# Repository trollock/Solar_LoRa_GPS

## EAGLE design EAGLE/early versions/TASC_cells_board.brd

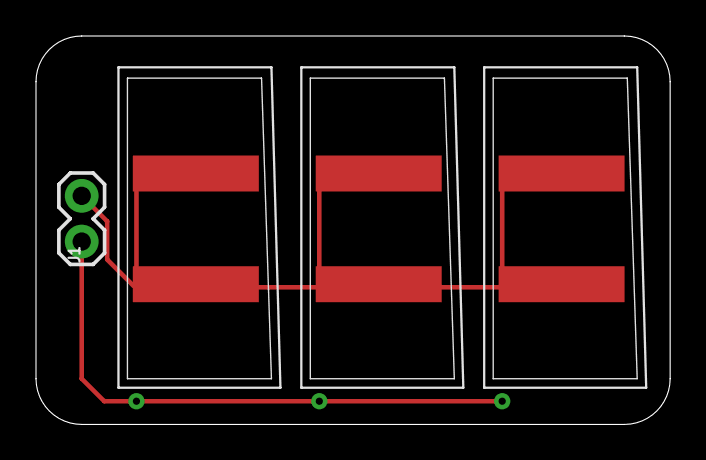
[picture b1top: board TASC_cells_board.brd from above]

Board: 2 copper layers, 35.2 x 21.6 mm, 4 parts (0 on the bottom side), 2 nets.

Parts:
J1: 1X02
U$1, U$2, U$3: TRISOLX_8X16

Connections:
NEG: J1.2, U$1.P$2, U$2.P$2, U$3.P$2
POS: J1.1, U$1.P$3, U$2.P$3, U$3.P$3

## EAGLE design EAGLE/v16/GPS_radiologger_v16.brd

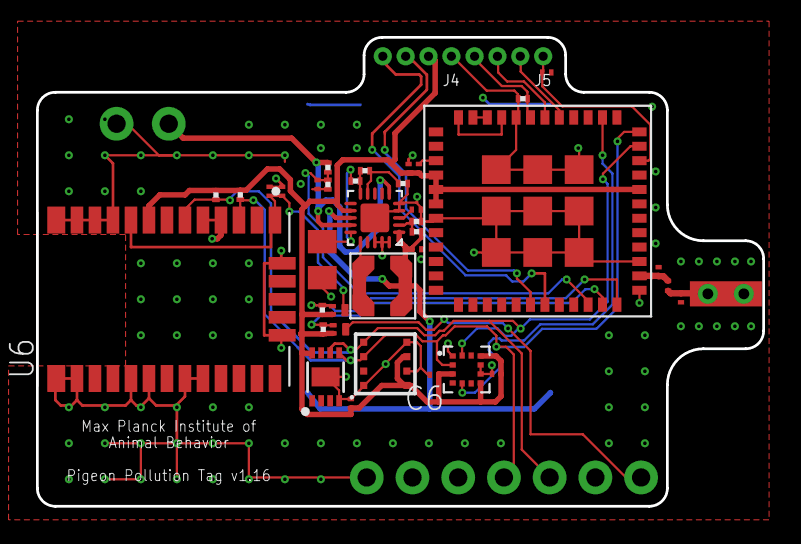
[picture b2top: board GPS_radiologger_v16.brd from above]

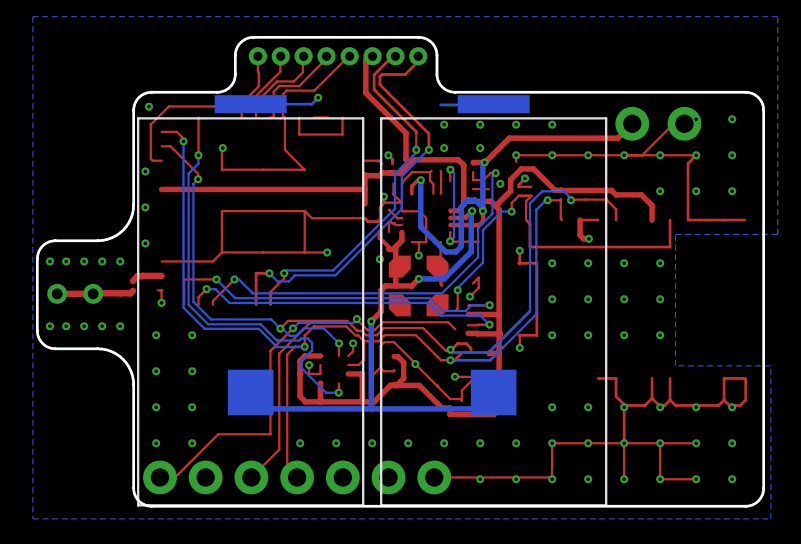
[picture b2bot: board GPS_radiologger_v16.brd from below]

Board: 2 copper layers, 40.4 x 26.1 mm, 44 parts (2 on the bottom side), 29 nets.

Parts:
C1, C3, C7, C10: 0.1 uF; C0201
C2: 47 uF; C0201
C4: 10nF; C0201
C5: 100 nF; C0201
C6, C8: C0201
C9: 1 uF; C0201
C11: 0.1uF; L0201
C13: 47 uF; C0805K
C14: 4.7 uF; C0201
IC4: CAT24M01HU5I-GT3; SON50P300X200X55-9N
J1, J3: 1X01_NO_SILK
J4, J5: 1X04_1.27MM_NO_SILK
J7: 1X07_NO_SILK
L3, L4: C0201
PDTA143TMB,1, PDTA143TMB,315: TINYPICO-PNPAMB; SOT883(B)
R1, R2: 4.7 k; R0201
R3: 10k; R0201
R4, R5: 100k; R0201
R6: 10 M; R0201
R7: 4.7 M; R0201
R8, R12: 3M; R0201
R9: 9.1M; R0201
R10: 6.2M; R0201
R11: 1M; R0201
U1: TYPEABZ
U2: BMA400; XDCR_BMA400
U4: SPV1050
U5: BME680BME680; LGA3.0X3.0
U6: CAM-M8Q-0; LCC100P960X1400X210-31N
U$1: LPS3015; LPS_3015
U$2: NITINOL_ANTENNA_SHORT; ICARUS_NITINOL_ANTENNA_SHORT
U$3, U$4: ICARUS_V4_RAW; ICARUS_FULL_TOP

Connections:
ACC_INT: U1.P$38, U2.5
BAT: J1.1, R7.2, U4.P$6, U4.P$14
BOOT: J5.4, R3.2, U1.P$43
GND: C1.2, C2.2, C3.2, C4.2, C5.2, C6.2, C7.2, C8.2, C9.1, C10.1, C13.2, C14.2, IC4.4, IC4.9, J3.1, J4.1, J7.1, J7.6, L3.2, L4.2, R3.1, R6.1, R9.1, R12.1, U1.P$3, U1.P$7, U1.P$25, U1.P$27, U1.P$44, U1.P$49, U1.P$50, U1.P$51, U1.P$52, U1.P$53, U1.P$54, U1.P$55, U1.P$56, U1.P$57, U2.1, U2.8, U2.9, U4.P$4, U4.P$5, U4.P$18, U4.P$19, U4.P$20, U4.P$21, U5.1, U5.5, U5.7, U6.4, U6.5, U6.10, U6.11, U6.12, U6.13, U6.14, U6.15, U6.18, U6.19, U6.21, U6.22, U6.27, U6.31, U$3.P$2, U$4.P$2
unnamed: U1.P$45, U1.P$48
unnamed: C11.2, L3.1, U1.P$26
unnamed: U4.P$16, U$1.P$2
unnamed: R8.1, R9.2, U4.P$2
unnamed: C14.1, R8.2, U4.P$1, U4.P$13, U$1.P$1, U$3.P$1, U$4.P$1
unnamed: R10.1, R11.2, U4.P$10
unnamed: R11.1, R12.2, U4.P$9
unnamed: C11.1, L4.1, U$2.1, U$2.2, U$2.3
unnamed: C13.1, R10.2, U4.P$15
unnamed: C4.1, U4.P$3
unnamed: U6.16, U6.17
POWER: C3.1, C6.1, C8.1, C9.2, C10.2, IC4.8, J4.2, PDTA143TMB,1.2, PDTA143TMB,315.2, R1.2, R2.2, R4.2, R5.2, U1.P$4, U1.P$5, U1.P$6, U1.P$32, U2.3, U2.7, U2.10, U4.P$12, U5.6, U5.8, U6.8
RST: C1.1, J5.1, U1.P$34
RX: J4.3, U1.P$18
SCD_PDTA: PDTA143TMB,1.1, R5.1, U1.P$23
SCD_PWR: J7.7, PDTA143TMB,1.3
SCL: IC4.6, J7.5, R2.1, U1.P$35, U2.12, U5.4, U6.6
SDA: IC4.5, J7.4, R1.1, U1.P$36, U2.2, U5.3, U6.3
SWDCLK: J5.3, U1.P$42
SWDIO: J5.2, U1.P$41
TCXO_OUT: U1.P$46, U1.P$47
TX: J4.4, U1.P$19
VOLT_MEAS: C7.1, R6.2, R7.1, U1.P$22
ZOE_PDTA: PDTA143TMB,315.1, R4.1, U1.P$24
ZOE_PWR: C2.1, C5.1, PDTA143TMB,315.3, U6.1, U6.9

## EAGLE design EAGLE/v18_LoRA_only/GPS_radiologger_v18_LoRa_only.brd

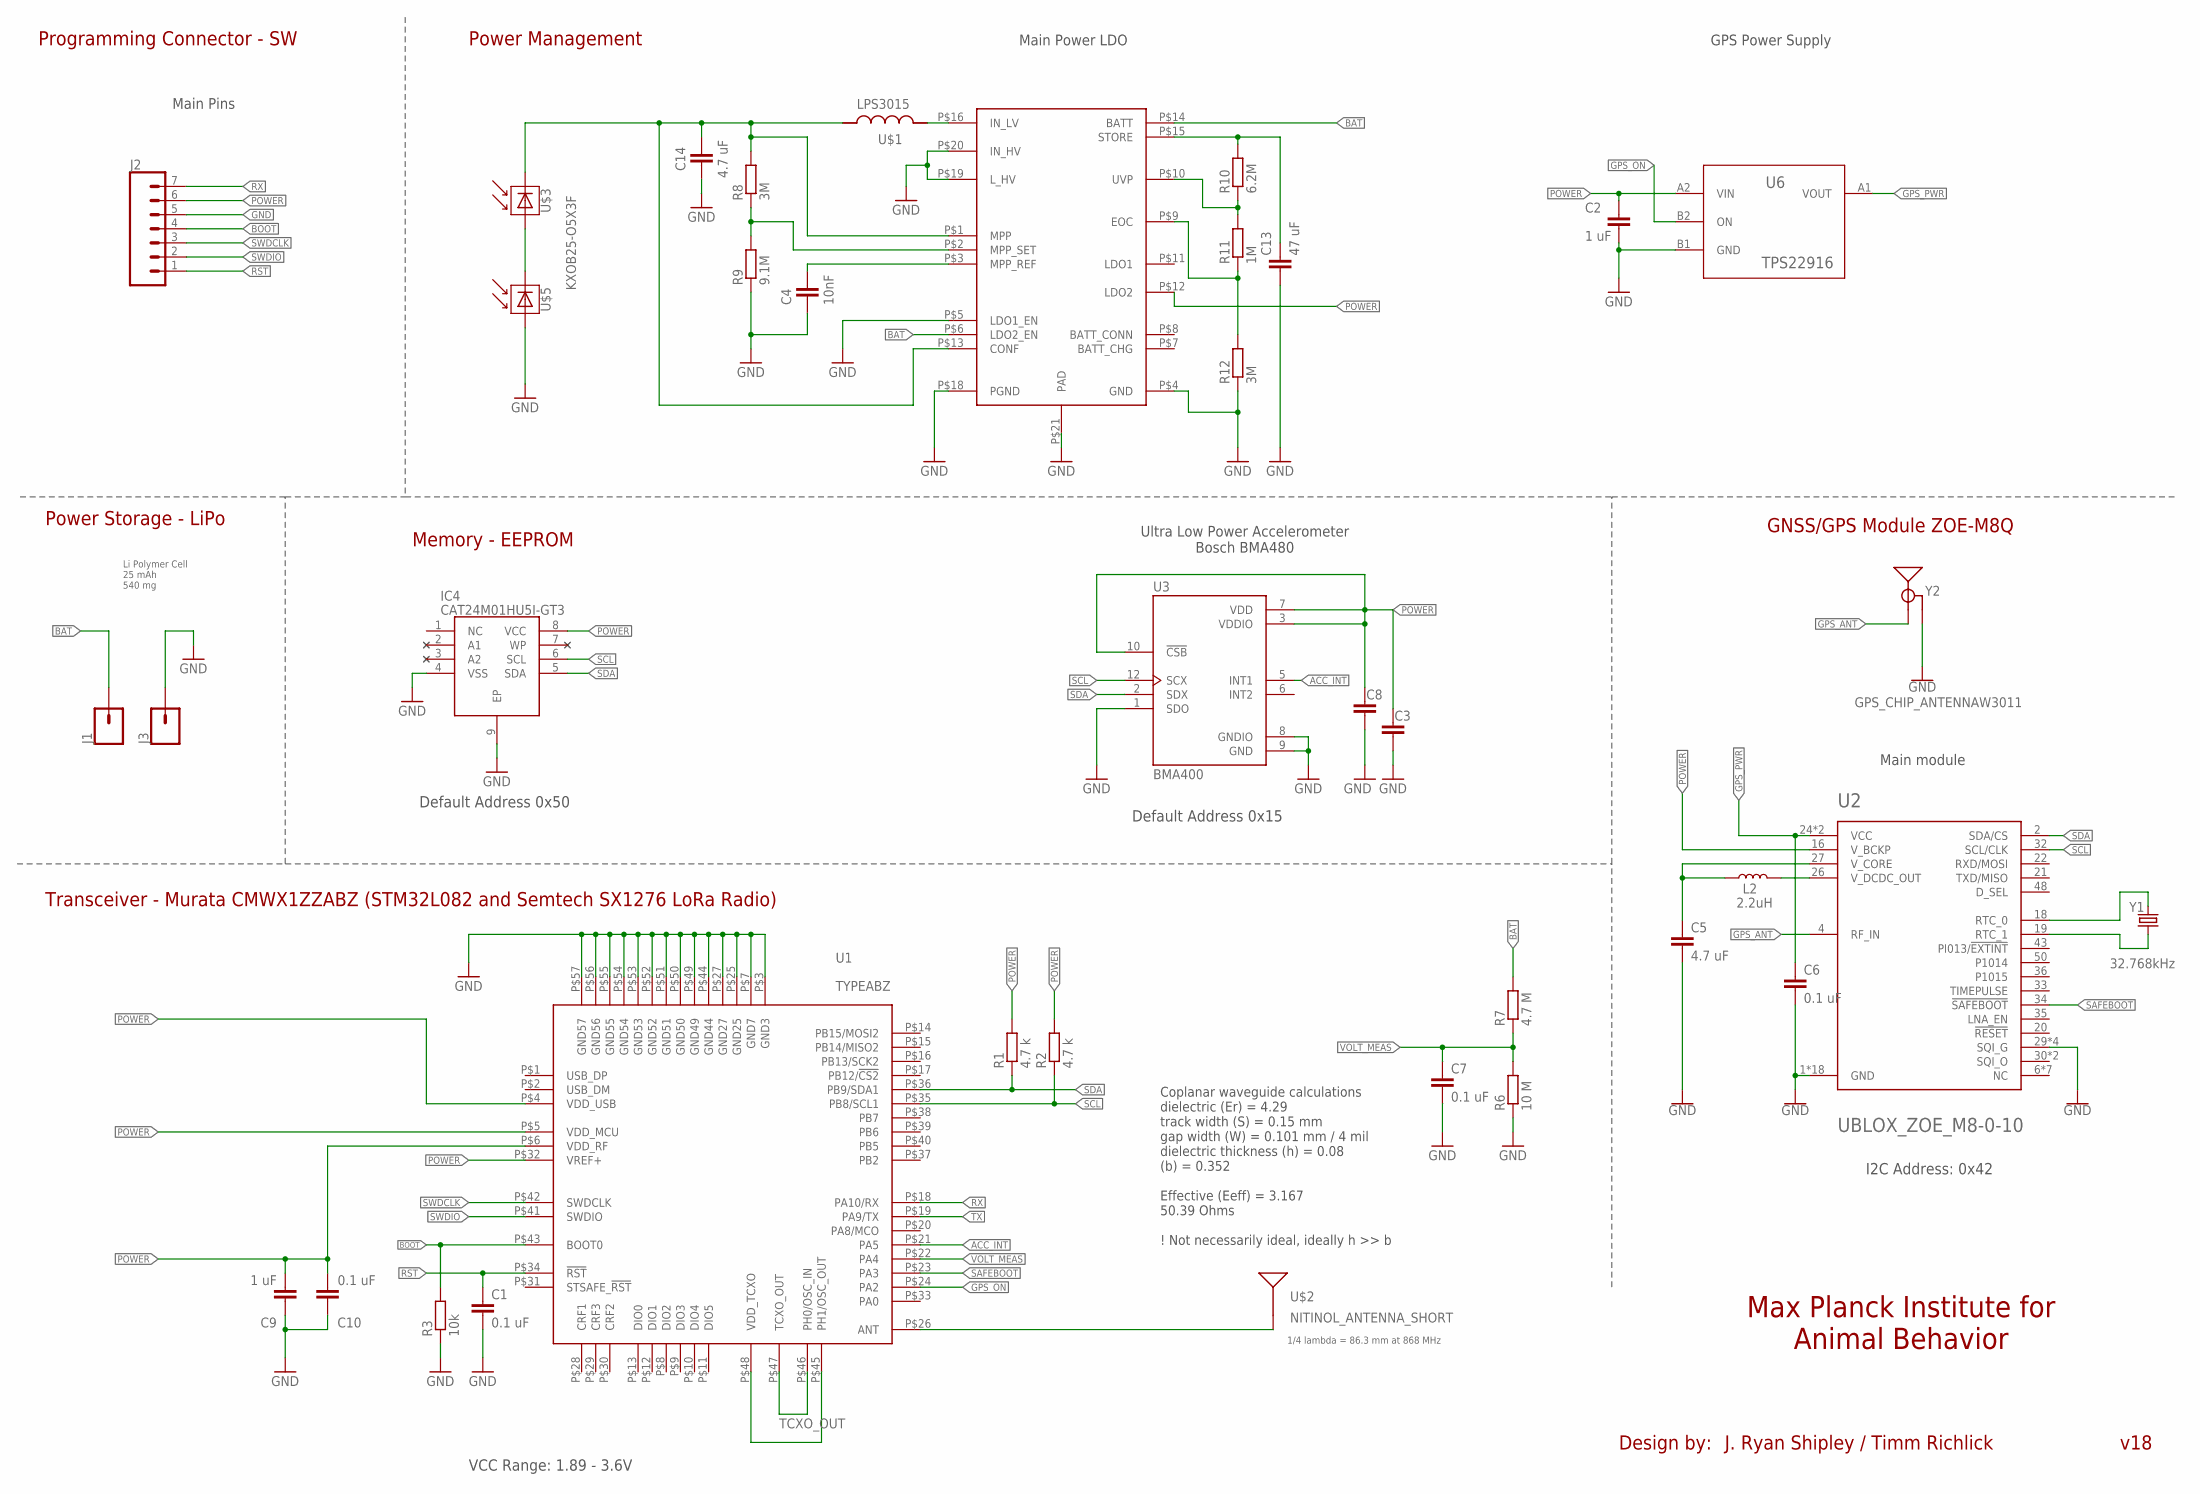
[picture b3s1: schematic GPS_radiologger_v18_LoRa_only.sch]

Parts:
C1, C6, C7, C10: 0.1 uF; C0201
C2, C9: 1 uF; C0201
C3, C8: C-EUC0201; C0201
C4: 10nF; C0201
C5, C14: 4.7 uF; C0201
C13: 47 uF; C0805K
IC4: CAT24M01HU5I-GT3; SON50P300X200X55-9N
J1, J3: CONN_01PTH_NO_SILK_YES_STOP; 1X01_NO_SILK
J2: CONN_07NO_SILK; 1X07_NO_SILK
L2: 2.2uH; 0806
R1, R2: 4.7 k; R0201
R3: 10k; R0201
R6: 10 M; R0201
R7: 4.7 M; R0201
R8, R12: 3M; R0201
R9: 9.1M; R0201
R10: 6.2M; R0201
R11: 1M; R0201
U1: TYPEABZ
U2: UBLOX_ZOE_M8-0-10
U3: BMA400; XDCR_BMA400
U4: SPV1050
U6: TPS22916
U$1: LPS3015; LPS_3015
U$2: NITINOL_ANTENNA_SHORT; ICARUS_NITINOL_ANTENNA_SHORT
U$3, U$5: KXOB25-O5X3F; KXOB25-05X3F
Y1: 32.768kHz; CRYSTAL-SMD-3.2X1.5MM
Y2: GPS_CHIP_ANTENNAW3011; W3011

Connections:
ACC_INT: U1.P$21 (PA5), U3.5 (INT1)
BAT: J1.1, R7.2, U4.P$6 (LDO2_EN), U4.P$14 (BATT)
BOOT: J2.4, R3.2, U1.P$43 (BOOT0)
GND: C1.2, C2.2, C3.2, C4.2, C5.2, C6.2, C7.2, C8.2, C9.1, C10.1, C13.2, C14.2, IC4.4 (VSS), IC4.9 (EP), J2.5, J3.1, R3.1, R6.1, R9.1, R12.1, U1.P$3 (GND3), U1.P$7 (GND7), U1.P$25 (GND25), U1.P$27 (GND27), U1.P$44 (GND44), U1.P$49 (GND49), U1.P$50 (GND50), U1.P$51 (GND51), U1.P$52 (GND52), U1.P$53 (GND53), U1.P$54 (GND54), U1.P$55 (GND55), U1.P$56 (GND56), U1.P$57 (GND57), U2.1 (GND), U2.3 (GND), U2.5 (GND), U2.7 (GND), U2.8 (GND), U2.9 (GND), U2.10 (GND), U2.11 (GND), U2.12 (GND), U2.17 (GND), U2.23 (GND), U2.29 (SQI_G), U2.31 (SQI_G), U2.37 (GND), U2.38 (GND), U2.39 (GND), U2.40 (GND), U2.41 (GND), U2.44 (GND), U2.46 (SQI_G), U2.47 (SQI_G), U2.49 (GND), U3.1 (SDO), U3.8 (GNDIO), U3.9 (GND), U4.P$4 (GND), U4.P$5 (LDO1_EN), U4.P$18 (PGND), U4.P$19 (L_HV), U4.P$20 (IN_HV), U4.P$21 (PAD), U6.B1 (GND), U$5.P$2 (MINUS), Y2.2 (GND), Y2.3 (GND)
GPS_ANT: U2.4 (RF_IN), Y2.1 (SIGNAL)
GPS_ON: U1.P$24 (PA2), U6.B2 (ON)
GPS_PWR: C6.1, U2.24 (VCC), U2.25 (VCC), U6.A1 (VOUT)
unnamed: U1.P$45 (PH1/OSC_OUT), U1.P$48 (VDD_TCXO)
unnamed: U$3.P$2 (MINUS), U$5.P$1 (PLUS)
unnamed: L2.2, U2.26 (V_DCDC_OUT)
unnamed: U4.P$16 (IN_LV), U$1.P$2 (2)
unnamed: C5.1, L2.1, U2.27 (V_CORE)
unnamed: R8.1, R9.2, U4.P$2 (MPP_SET)
unnamed: C14.1, R8.2, U4.P$1 (MPP), U4.P$13 (CONF), U$1.P$1 (1), U$3.P$1 (PLUS)
unnamed: R10.1, R11.2, U4.P$10 (UVP)
unnamed: R11.1, R12.2, U4.P$9 (EOC)
unnamed: U1.P$26 (ANT), U$2.1, U$2.2, U$2.3
unnamed: C13.1, R10.2, U4.P$15 (STORE)
unnamed: C4.1, U4.P$3 (MPP_REF)
unnamed: U2.18 (RTC_0), Y1.P$2 (2)
unnamed: U2.19 (RTC_1), Y1.P$1 (1)
POWER: C2.1, C3.1, C8.1, C9.2, C10.2, IC4.8 (VCC), J2.6, R1.2, R2.2, U1.P$4 (VDD_USB), U1.P$5 (VDD_MCU), U1.P$6 (VDD_RF), U1.P$32 (VREF+), U2.16 (V_BCKP), U3.3 (VDDIO), U3.7 (VDD), U3.10 (!CSB), U4.P$12 (LDO2), U6.A2 (VIN)
RST: C1.1, J2.1, U1.P$34 (!RST)
RX: J2.7, U1.P$18 (PA10/RX)
SAFEBOOT: U1.P$23 (PA3), U2.34 (!SAFEBOOT)
SCL: IC4.6 (SCL), R2.1, U1.P$35 (PB8/SCL1), U2.32 (SCL/CLK), U3.12 (SCX)
SDA: IC4.5 (SDA), R1.1, U1.P$36 (PB9/SDA1), U2.2 (SDA/CS), U3.2 (SDX)
SWDCLK: J2.3, U1.P$42 (SWDCLK)
SWDIO: J2.2, U1.P$41 (SWDIO)
TCXO_OUT: U1.P$46 (PH0/OSC_IN), U1.P$47 (TCXO_OUT)
TX: U1.P$19 (PA9/TX)
VOLT_MEAS: C7.1, R6.2, R7.1, U1.P$22 (PA4)

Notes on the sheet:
GNSS/GPS Module ZOE-M8Q
VCC Range: 1.89 - 3.6V
Max Planck Institute for Animal Behavior
Transceiver - Murata CMWX1ZZABZ (STM32L082 and Semtech SX1276 LoRa Radio)
Programming Connector - SW
Power Storage - LiPo
Design by:
J. Ryan Shipley / Timm Richlick
v18
Li Polymer Cell 25 mAh 540 mg
Power Management
Main Power LDO
Memory - EEPROM
Main module
Coplanar waveguide calculations dielectric (Er) = 4.29 track width (S) = 0.15 mm gap width (W) = 0.101 mm / 4 mil dielectric thickness (h) = 0.08 (b) = 0.352 Effective (Eeff) = 3.167 50.39 Ohms ! Not necessarily ideal, ideally h >> b
Main Pins
Default Address 0x50
1/4 lambda = 86.3 mm at 868 MHz
GPS Power Supply
I2C Address: 0x42
Ultra Low Power Accelerometer Bosch BMA480
Default Address 0x15

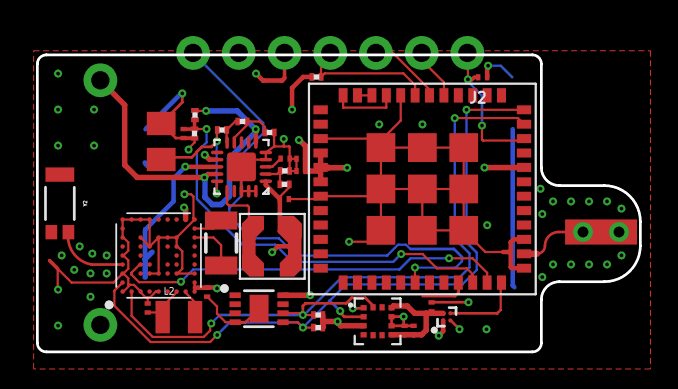
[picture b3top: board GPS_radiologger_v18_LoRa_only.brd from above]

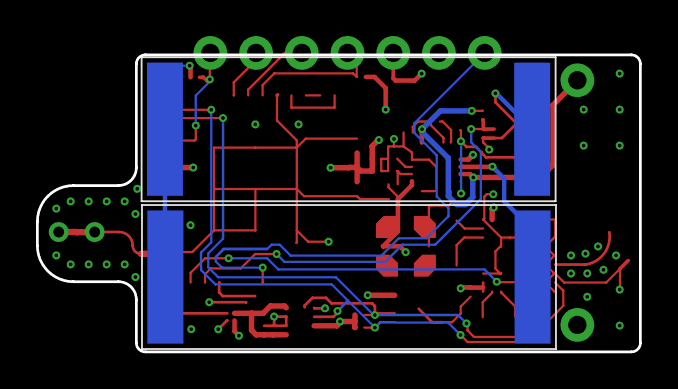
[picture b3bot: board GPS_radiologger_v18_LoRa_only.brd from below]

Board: 4 copper layers, 33.5 x 16.5 mm, 38 parts (2 on the bottom side), 31 nets.

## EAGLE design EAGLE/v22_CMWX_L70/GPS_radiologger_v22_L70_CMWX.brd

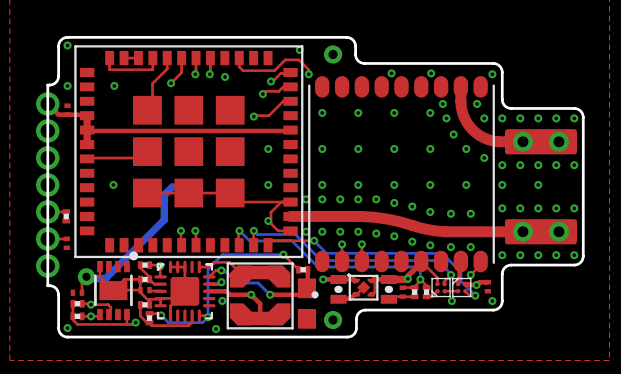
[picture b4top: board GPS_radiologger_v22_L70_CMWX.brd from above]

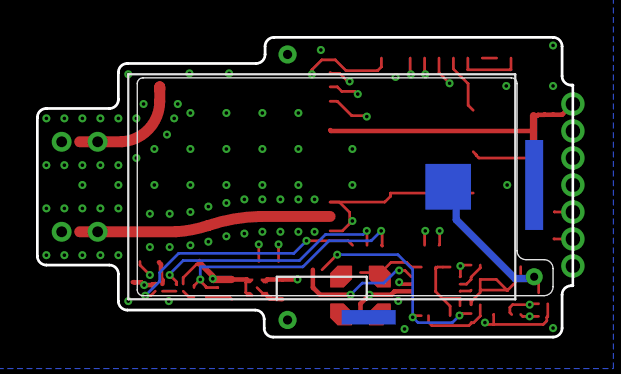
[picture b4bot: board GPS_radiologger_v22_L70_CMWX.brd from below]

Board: 4 copper layers, 29.8 x 16.6 mm, 34 parts (2 on the bottom side), 28 nets.

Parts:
C1, C7: 0.1 uF; C0201
C2, C9: 1 uF; C0201
C4: 10nF; C0201
C13: 47 uF; C0603
C14: 4.7 uF; C0201
C17, C18: 1 uF; 0402-CAP
IC4: CAT24M01HU5I-GT3; SON50P300X200X55-9N
J1, J3: 1X01_SMALL
R1, R2: 4.7 k; R0201
R3: 10k; R0201
R6: 300 K; R0201
R7: 150 K; R0201
R8, R12: 3M; R0201
R9: 9.1M; R0201
R10: 6.2M; R0201
R11: 1M; R0201
U1: TYPEABZ
U2: L70; XCVR_L70
U3, U6: TPS22907YZT; YFP0004-DSBGA
U4: SPV1050
U5: NCP161
U$1: LPS3015; LPS_3015
U$2, U$4: NITINOL_ANTENNA_SHORT; ICARUS_NITINOL_ANTENNA_SHORT
U$3: ICARUS_FULL
U$5: CASTELLATED_7_PIN
U$6: ICARUS_V4_FOOTPRINT; ICARUS_FULL_FOOTPRINT

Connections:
BAT: C17.1, J1.P$1, U2.6, U3.A2, U4.P$14, U5.P$3, U5.P$4, U$5.P$1
BOOT: R3.2, U1.P$43, U$5.P$3
GND: C1.2, C2.2, C4.2, C7.2, C9.1, C13.2, C14.2, C17.2, C18.2, IC4.4, IC4.9, J3.P$1, R3.1, R6.1, R9.1, R12.1, U1.P$3, U1.P$7, U1.P$25, U1.P$27, U1.P$44, U1.P$49, U1.P$50, U1.P$51, U1.P$52, U1.P$53, U1.P$54, U1.P$55, U1.P$56, U1.P$57, U2.1, U2.10, U2.12, U3.B1, U4.P$4, U4.P$5, U4.P$6, U4.P$18, U4.P$19, U4.P$20, U4.P$21, U5.P$2, U5.P$5, U6.B1, U$3.P$2, U$5.P$4, U$6.P$2
GPS_ON: U1.P$24, U6.B2
GPS_PWR: U2.8, U6.A1
GPS_RST: U1.P$39, U2.9
unnamed: U1.P$45, U1.P$48
unnamed: U2.11, U$4.1, U$4.2, U$4.3
unnamed: U4.P$16, U$1.P$2
unnamed: R8.1, R9.2, U4.P$2
unnamed: R7.2, U3.A1
unnamed: R10.1, R11.2, U4.P$10
unnamed: R11.1, R12.2, U4.P$9
unnamed: U1.P$26, U$2.1, U$2.2, U$2.3
unnamed: C4.1, U4.P$3
POWER: C2.1, C9.2, C18.1, IC4.8, R1.2, R2.2, U1.P$4, U1.P$5, U1.P$6, U1.P$32, U5.P$1, U6.A2, U$5.P$7
RST: C1.1, U1.P$34, U$5.P$2
RX: U1.P$18, U2.2
SCL: IC4.6, R2.1, U1.P$35
SDA: IC4.5, R1.1, U1.P$36
SOL_IN: C14.1, R8.2, U4.P$1, U4.P$13, U$1.P$1, U$3.P$1, U$6.P$1
SWDCLK: U1.P$42, U$5.P$6
SWDIO: U1.P$41, U$5.P$5
TCXO_OUT: U1.P$46, U1.P$47
TX: U1.P$19, U2.3
VOLT_MEAS: C7.1, R6.2, R7.1, U1.P$22
VOLT_ON: U1.P$23, U3.B2
V_STORE: C13.1, R10.2, U4.P$15

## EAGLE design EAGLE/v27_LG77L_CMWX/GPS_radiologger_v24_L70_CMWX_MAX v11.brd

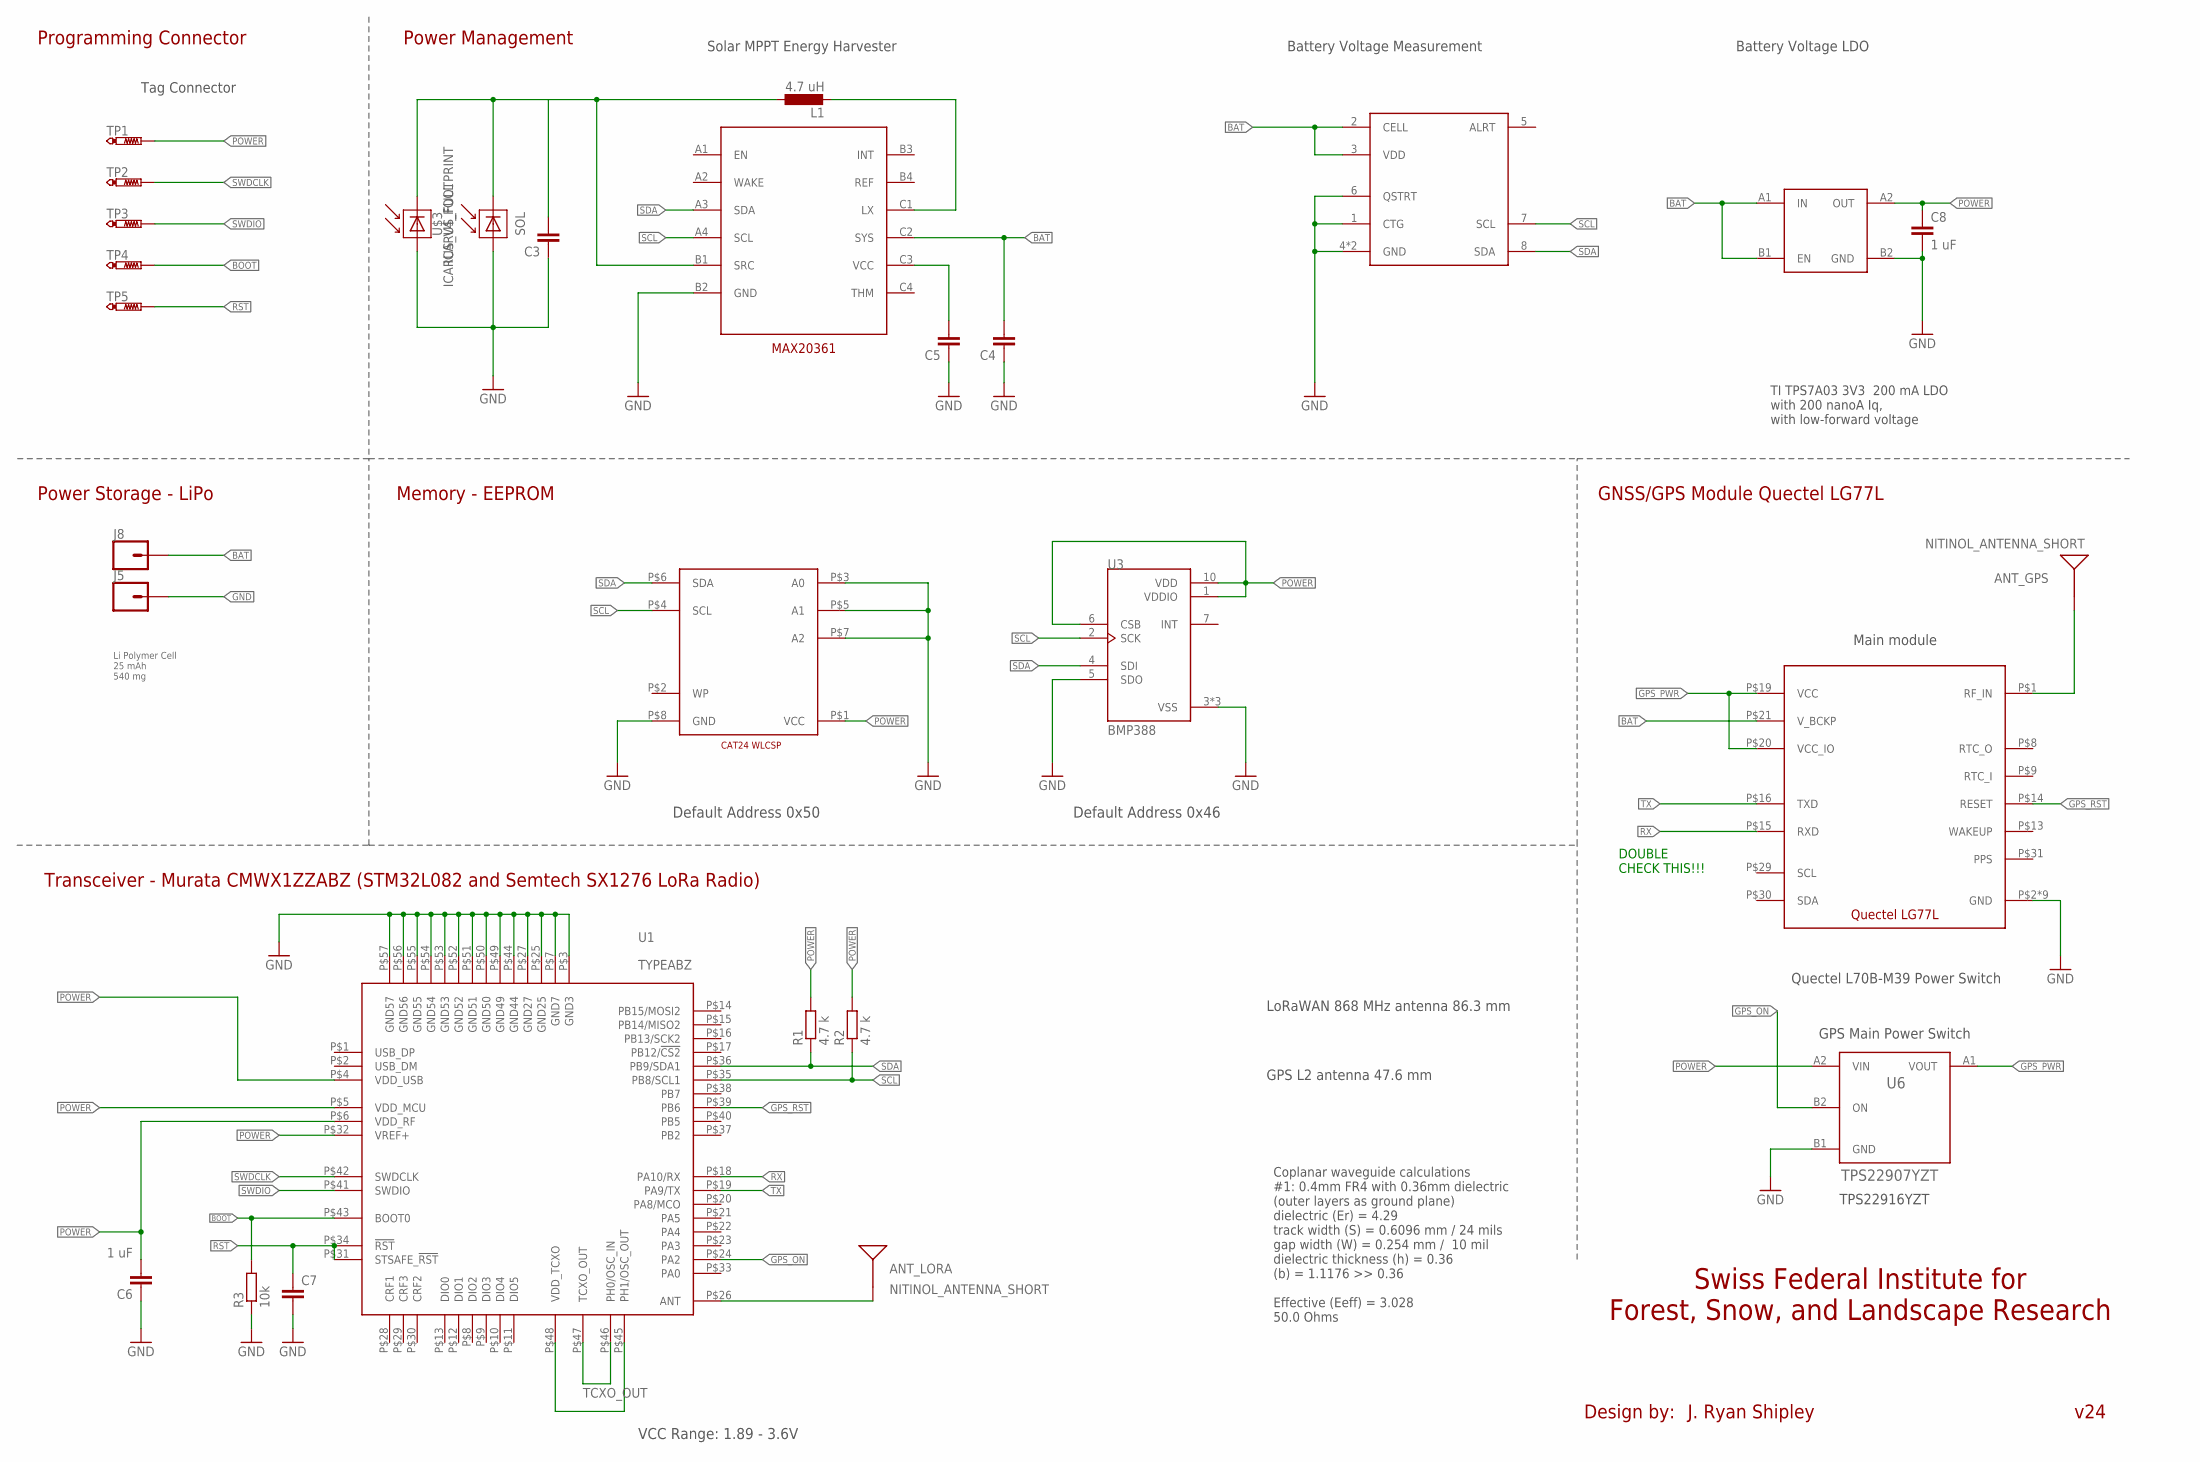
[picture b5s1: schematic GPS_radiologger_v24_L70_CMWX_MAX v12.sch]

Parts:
ANT_GPS: NITINOL_ANTENNA_SHORT; ICARUS_NITINOL_ANTENNA_SHORT
ANT_LORA: NITINOL_ANTENNA_SHORT; ICARUS_NITINOL_ANTENNA_SHORT
C3: 10UF; 0603-TIGHT
C4, C5: 1.0UF; 0402-TIGHTER
C6, C8: 1 uF; 0402-TIGHTER
C7: C-EUC0201; C0201
J5, J8: CONN_01PTH_NO_SILK_SMALL; 1X01_SMALL
L1: 4.7 uH; INDC2016X120L
R1, R2: 4.7 k; R0201
R3: 10k; R0201
SOL: ICARUS_V4_FOOTPRINT; ICARUS_FULL_FOOTPRINT
TP1, TP2, TP3, TP4, TP5: PTR1TP08SQ; TP08SQ
U1: TYPEABZ
U2: LG77L
U3: BMP388; PQFN50P200X200X80-10N
U4: TPS7A03-DSBGA; BGA4N35P2X2_70X70X40N
U5: MAX17048G+; SON50P200X200X75-9T80X120L
U6: TPS22907YZT; YFP0004-DSBGA
U7: CAT24_WLCSP8; WLCSP8
U8: MAX20361; BGA12N40P4X3_123X163X64N
U$3: ICARUS_FULL

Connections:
BAT: C4.P$2 (2), J8.P$1, U2.P$21 (V_BCKP), U4.A1 (IN), U4.B1 (EN), U5.2 (CELL), U5.3 (VDD), U8.C2 (SYS); also elsewhere on the board
BOOT: R3.2, TP4.TP, U1.P$43 (BOOT0)
GND: C3.P$1 (1), C4.P$1 (1), C5.P$1 (1), C6.P$1 (1), C7.2, C8.P$2 (2), J5.P$1, R3.1, SOL.P$2 (MINUS), U1.P$3 (GND3), U1.P$7 (GND7), U1.P$25 (GND25), U1.P$27 (GND27), U1.P$44 (GND44), U1.P$49 (GND49), U1.P$50 (GND50), U1.P$51 (GND51), U1.P$52 (GND52), U1.P$53 (GND53), U1.P$54 (GND54), U1.P$55 (GND55), U1.P$56 (GND56), U1.P$57 (GND57), U2.P$2 (GND), U3.3 (VSS), U3.5 (SDO), U3.8 (VSS), U3.9 (VSS), U4.B2 (GND), U5.1 (CTG), U5.4 (GND), U5.6 (QSTRT), U6.B1 (GND), U7.P$3 (A0), U7.P$5 (A1), U7.P$7 (A2), U7.P$8 (GND), U8.B2 (GND), U$3.P$2 (MINUS); also elsewhere on the board
GPS_ON: U1.P$24 (PA2), U6.B2 (ON)
GPS_PWR: U2.P$19 (VCC), U2.P$20 (VCC_IO), U6.A1 (VOUT); also elsewhere on the board
GPS_RST: U1.P$39 (PB6), U2.P$14 (RESET); also elsewhere on the board
unnamed: U1.P$45 (PH1/OSC_OUT), U1.P$48 (VDD_TCXO)
unnamed 7: ANT_GPS.1, ANT_GPS.2, ANT_GPS.3, U2.P$1 (RF_IN); also elsewhere on the board
unnamed: L1.2, U8.C1 (LX)
unnamed: C5.P$2 (2), U8.C3 (VCC)
unnamed: ANT_LORA.1, ANT_LORA.2, ANT_LORA.3, U1.P$26 (ANT)
unnamed: C3.P$2 (2), L1.1, SOL.P$1 (PLUS), U8.B1 (SRC), U$3.P$1 (PLUS)
POWER: C6.P$2 (2), C8.P$1 (1), R1.2, R2.2, TP1.TP, U1.P$4 (VDD_USB), U1.P$5 (VDD_MCU), U1.P$6 (VDD_RF), U1.P$32 (VREF+), U3.1 (VDDIO), U3.6 (CSB), U3.10 (VDD), U4.A2 (OUT), U6.A2 (VIN), U7.P$1 (VCC)
RST: C7.1, TP5.TP, U1.P$31 (STSAFE_!RST), U1.P$34 (!RST)
RX: U1.P$18 (PA10/RX), U2.P$15 (RXD); also elsewhere on the board
SCL: R2.1, U1.P$35 (PB8/SCL1), U3.2 (SCK), U5.7 (SCL), U7.P$4 (SCL), U8.A4 (SCL); also elsewhere on the board
SDA: R1.1, U1.P$36 (PB9/SDA1), U3.4 (SDI), U5.8 (SDA), U7.P$6 (SDA), U8.A3 (SDA); also elsewhere on the board
SWDCLK: TP2.TP, U1.P$42 (SWDCLK)
SWDIO: TP3.TP, U1.P$41 (SWDIO)
TCXO_OUT: U1.P$46 (PH0/OSC_IN), U1.P$47 (TCXO_OUT)
TX: U1.P$19 (PA9/TX), U2.P$16 (TXD); also elsewhere on the board

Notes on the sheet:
GNSS/GPS Module Quectel LG77L
VCC Range: 1.89 - 3.6V
Swiss Federal Institute for Forest, Snow, and Landscape Research
Transceiver - Murata CMWX1ZZABZ (STM32L082 and Semtech SX1276 LoRa Radio)
Programming Connector
Power Storage - LiPo
Design by:
J. Ryan Shipley
v24
Li Polymer Cell 25 mAh 540 mg
Power Management
Solar MPPT Energy Harvester
Memory - EEPROM
Main module
Coplanar waveguide calculations #1: 0.4mm FR4 with 0.36mm dielectric (outer layers as ground plane) dielectric (Er) = 4.29 track width (S) = 0.6096 mm / 24 mils gap width (W) = 0.254 mm / 10 mil dielectric thickness (h) = 0.36 (b) = 1.1176 >> 0.36 Effective (Eeff) = 3.028 50.0 Ohms
Tag Connector
Default Address 0x50
GPS Main Power Switch
TI TPS7A03 3V3 200 mA LDO with 200 nanoA Iq, with low-forward voltage
Quectel L70B-M39 Power Switch
Battery Voltage Measurement
Battery Voltage LDO
Default Address 0x46
TPS22916YZT
GPS L2 antenna 47.6 mm
LoRaWAN 868 MHz antenna 86.3 mm
DOUBLE CHECK THIS!!!

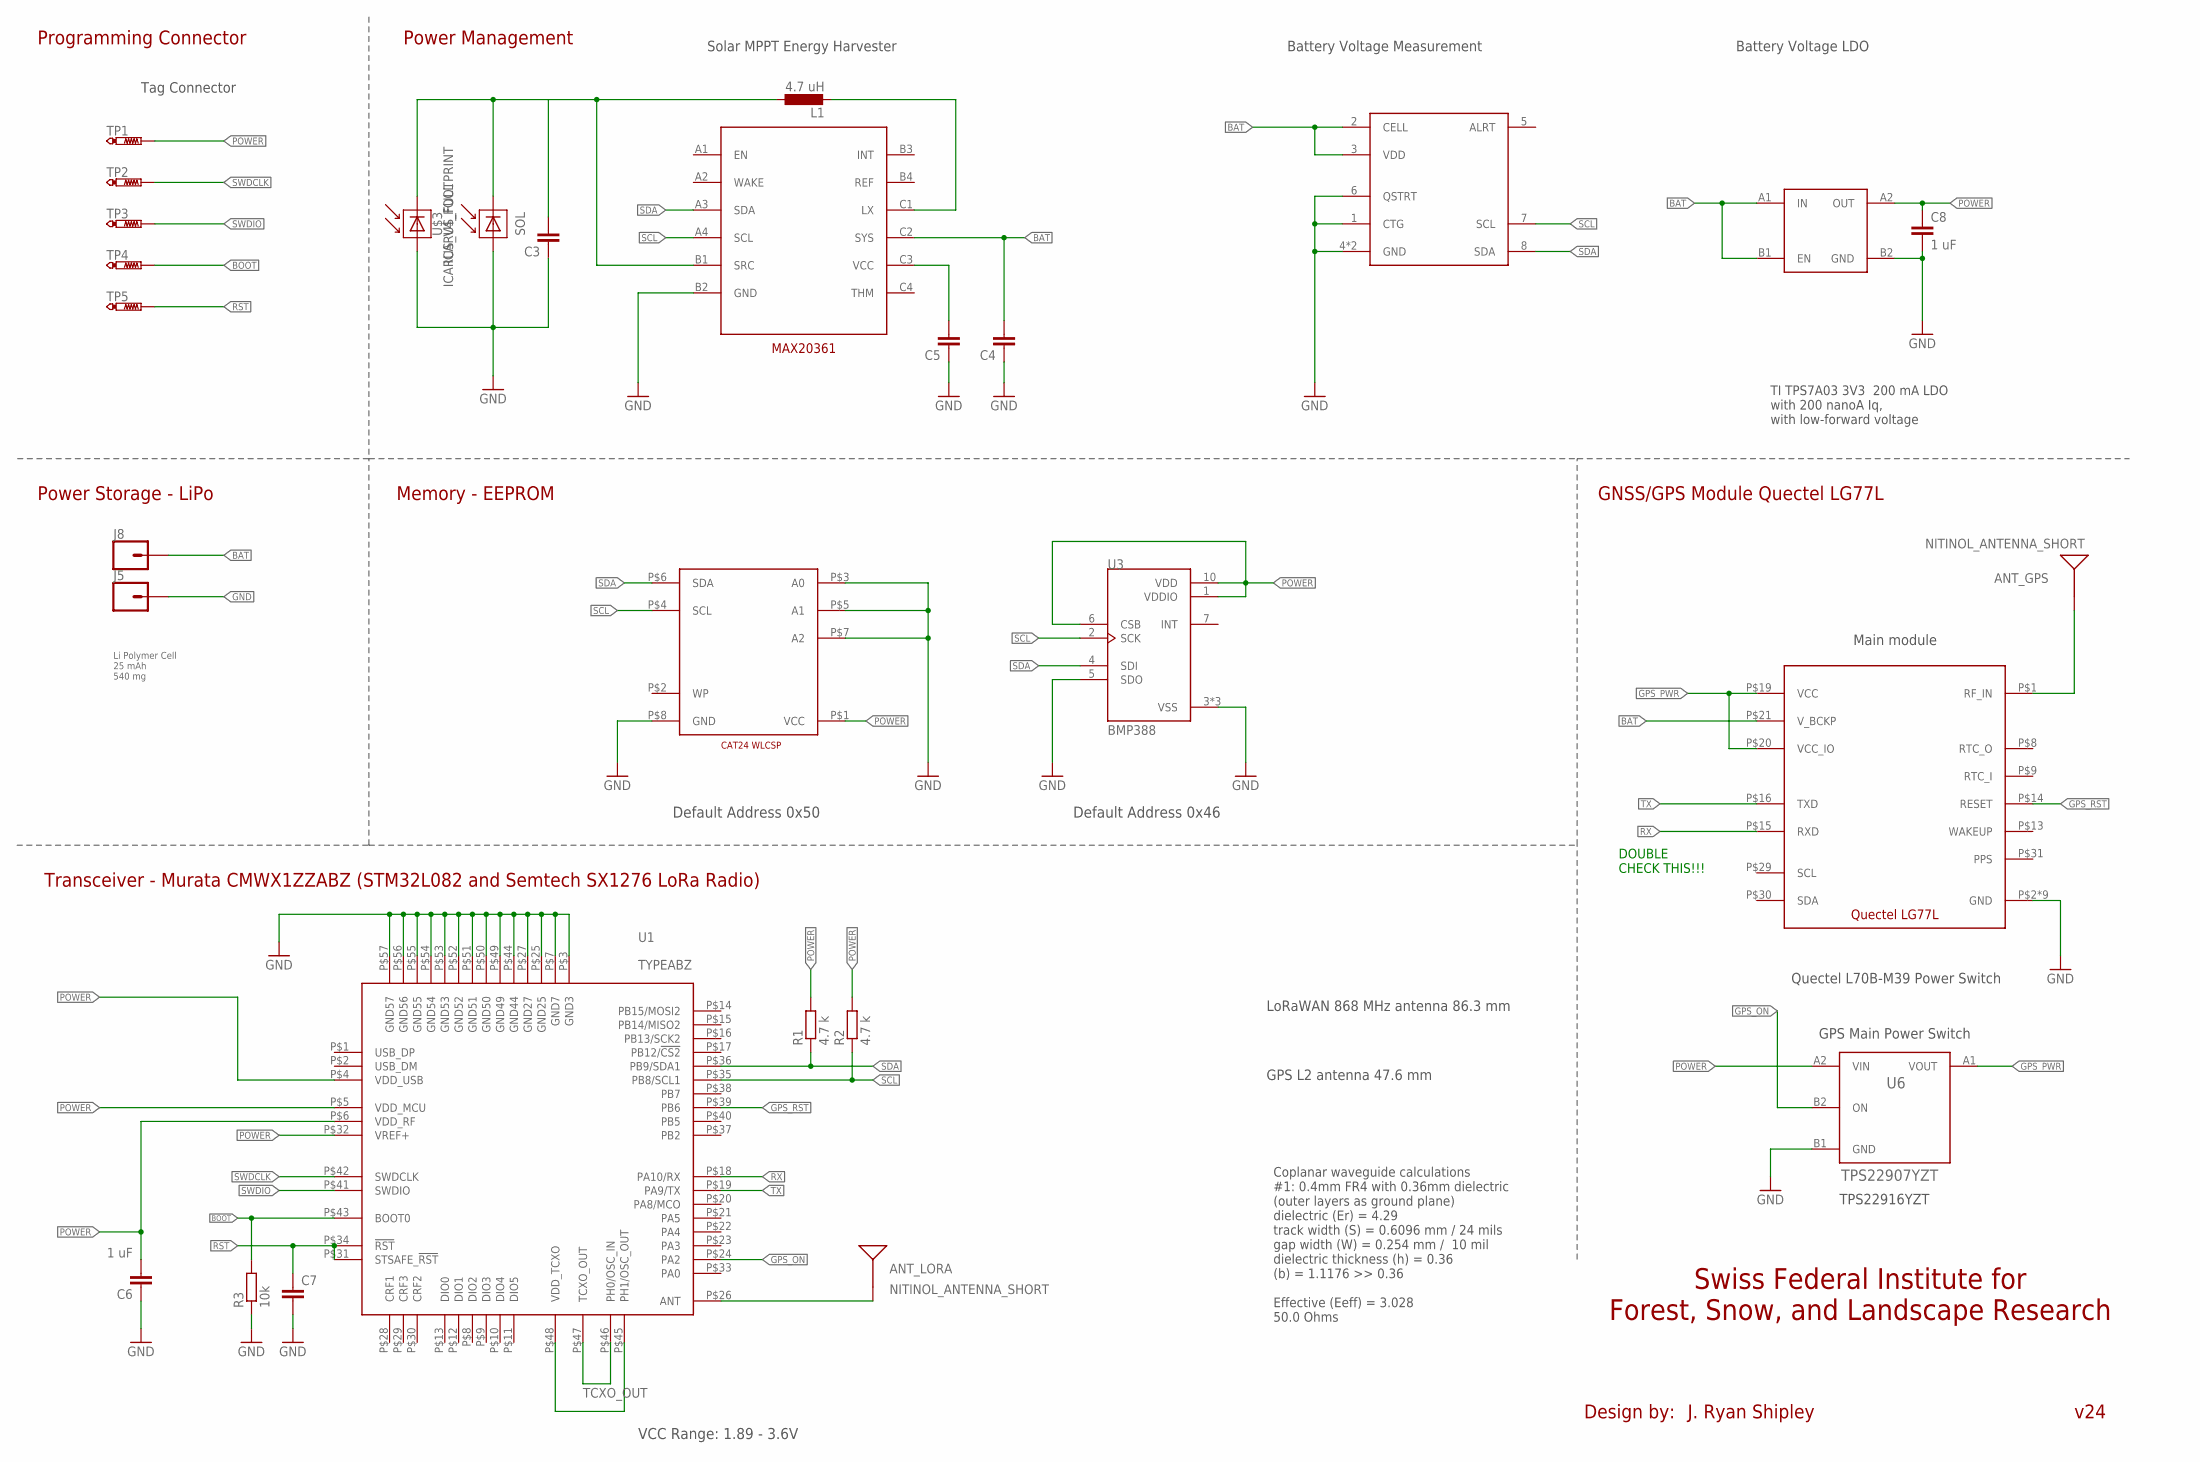
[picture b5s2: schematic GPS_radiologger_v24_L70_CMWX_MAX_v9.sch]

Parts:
ANT_GPS: NITINOL_ANTENNA_SHORT; ICARUS_NITINOL_ANTENNA_SHORT
ANT_LORA: NITINOL_ANTENNA_SHORT; ICARUS_NITINOL_ANTENNA_SHORT
C3: 10UF; 0603-TIGHT
C4, C5: 1.0UF; 0402-TIGHTER
C6, C8: 1 uF; 0402-TIGHTER
C7: C-EUC0201; C0201
J5, J8: CONN_01PTH_NO_SILK_SMALL; 1X01_SMALL
L1: 4.7 uH; INDC2016X120L
R1, R2: 4.7 k; R0201
R3: 10k; R0201
SOL: ICARUS_V4_FOOTPRINT; ICARUS_FULL_FOOTPRINT
TP1, TP2, TP3, TP4, TP5: PTR1TP08SQ; TP08SQ
U1: TYPEABZ
U3: BMP388; PQFN50P200X200X80-10N
U4: TPS7A03-DSBGA; BGA4N35P2X2_70X70X40N
U6: TPS22907YZT; YFP0004-DSBGA
U7: CAT24_WLCSP8; WLCSP8
U8: MAX20361; BGA12N40P4X3_123X163X64N
U$1: LG77L
U$2: MAX17048G+; SON50P200X200X75-9T80X120L
U$3: ICARUS_FULL

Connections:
BAT: C4.P$2 (2), J8.P$1, U4.A1 (IN), U4.B1 (EN), U8.C2 (SYS), U$1.P$21 (V_BCKP), U$2.2 (CELL), U$2.3 (VDD); also elsewhere on the board
BOOT: R3.2, TP4.TP, U1.P$43 (BOOT0)
GND: C3.P$1 (1), C4.P$1 (1), C5.P$1 (1), C6.P$1 (1), C7.2, C8.P$2 (2), J5.P$1, R3.1, SOL.P$2 (MINUS), U1.P$3 (GND3), U1.P$7 (GND7), U1.P$25 (GND25), U1.P$27 (GND27), U1.P$44 (GND44), U1.P$49 (GND49), U1.P$50 (GND50), U1.P$51 (GND51), U1.P$52 (GND52), U1.P$53 (GND53), U1.P$54 (GND54), U1.P$55 (GND55), U1.P$56 (GND56), U1.P$57 (GND57), U3.3 (VSS), U3.5 (SDO), U3.8 (VSS), U3.9 (VSS), U4.B2 (GND), U6.B1 (GND), U7.P$3 (A0), U7.P$5 (A1), U7.P$7 (A2), U7.P$8 (GND), U8.B2 (GND), U$1.P$2 (GND), U$1.P$18 (GND), U$1.P$37 (GND), U$1.P$38 (GND), U$1.P$39 (GND), U$1.P$40 (GND), U$1.P$41 (GND), U$1.P$42 (GND), U$1.P$43 (GND), U$2.1 (CTG), U$2.4 (GND), U$2.6 (QSTRT), U$2.9 (GND), U$3.P$2 (MINUS); also elsewhere on the board
GPS_ON: U1.P$24 (PA2), U6.B2 (ON)
GPS_PWR: U6.A1 (VOUT), U$1.P$19 (VCC), U$1.P$20 (VCC_IO); also elsewhere on the board
GPS_RST: U1.P$39 (PB6), U$1.P$14 (RESET); also elsewhere on the board
unnamed: U1.P$45 (PH1/OSC_OUT), U1.P$48 (VDD_TCXO)
unnamed 7: ANT_GPS.1, ANT_GPS.2, ANT_GPS.3, U$1.P$1 (RF_IN); also elsewhere on the board
unnamed: L1.2, U8.C1 (LX)
unnamed: C5.P$2 (2), U8.C3 (VCC)
unnamed: ANT_LORA.1, ANT_LORA.2, ANT_LORA.3, U1.P$26 (ANT)
unnamed: C3.P$2 (2), L1.1, SOL.P$1 (PLUS), U8.B1 (SRC), U$3.P$1 (PLUS)
POWER: C6.P$2 (2), C8.P$1 (1), R1.2, R2.2, TP1.TP, U1.P$4 (VDD_USB), U1.P$5 (VDD_MCU), U1.P$6 (VDD_RF), U1.P$32 (VREF+), U3.1 (VDDIO), U3.6 (CSB), U3.10 (VDD), U4.A2 (OUT), U6.A2 (VIN), U7.P$1 (VCC)
RST: C7.1, TP5.TP, U1.P$31 (STSAFE_!RST), U1.P$34 (!RST)
RX: U1.P$18 (PA10/RX), U$1.P$15 (RXD); also elsewhere on the board
SCL: R2.1, U1.P$35 (PB8/SCL1), U3.2 (SCK), U7.P$4 (SCL), U8.A4 (SCL), U$2.7 (SCL); also elsewhere on the board
SDA: R1.1, U1.P$36 (PB9/SDA1), U3.4 (SDI), U7.P$6 (SDA), U8.A3 (SDA), U$2.8 (SDA); also elsewhere on the board
SWDCLK: TP2.TP, U1.P$42 (SWDCLK)
SWDIO: TP3.TP, U1.P$41 (SWDIO)
TCXO_OUT: U1.P$46 (PH0/OSC_IN), U1.P$47 (TCXO_OUT)
TX: U1.P$19 (PA9/TX), U$1.P$16 (TXD); also elsewhere on the board

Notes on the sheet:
GNSS/GPS Module Quectel LG77L
VCC Range: 1.89 - 3.6V
Swiss Federal Institute for Forest, Snow, and Landscape Research
Transceiver - Murata CMWX1ZZABZ (STM32L082 and Semtech SX1276 LoRa Radio)
Programming Connector
Power Storage - LiPo
Design by:
J. Ryan Shipley
v24
Li Polymer Cell 25 mAh 540 mg
Power Management
Solar MPPT Energy Harvester
Memory - EEPROM
Main module
Coplanar waveguide calculations #1: 0.4mm FR4 with 0.36mm dielectric (outer layers as ground plane) dielectric (Er) = 4.29 track width (S) = 0.6096 mm / 24 mils gap width (W) = 0.254 mm / 10 mil dielectric thickness (h) = 0.36 (b) = 1.1176 >> 0.36 Effective (Eeff) = 3.028 50.0 Ohms
Tag Connector
Default Address 0x50
GPS Main Power Switch
TI TPS7A03 3V3 200 mA LDO with 200 nanoA Iq, with low-forward voltage
Quectel L70B-M39 Power Switch
Battery Voltage Measurement
Battery Voltage LDO
Default Address 0x46
TPS22916YZT
GPS L2 antenna 47.6 mm
LoRaWAN 868 MHz antenna 86.3 mm
DOUBLE CHECK THIS!!!

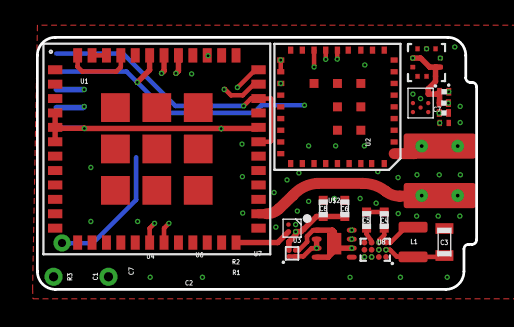
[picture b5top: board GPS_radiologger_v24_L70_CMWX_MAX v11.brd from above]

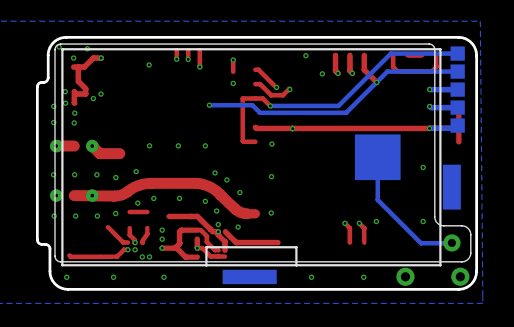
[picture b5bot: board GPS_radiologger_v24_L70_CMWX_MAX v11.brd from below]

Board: 4 copper layers, 24.4 x 14.0 mm, 29 parts (8 on the bottom side), 21 nets.

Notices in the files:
parts and their libraries:
SparkFun-Connectors: Licensing: Creative Commons ShareAlike 4.0 International - https://creativecommons.org/licenses/by-sa/4.0
